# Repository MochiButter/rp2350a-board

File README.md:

# rp2350a-board
A simple development board featuring the rp2350a microcontroller.

## Changes from the Pico 2

- PICO_DEFAULT_LED_PIN is now IO15
- Flash size increased to 128Mbit
- ESD protection on the usb data wires
- A reset button
- An LDO voltage regulator
- USB-C receptacle

`blink` and `hello_usb` of the examples worked on the board as expected.

Licensed under CERN-OHL-P v2 or later

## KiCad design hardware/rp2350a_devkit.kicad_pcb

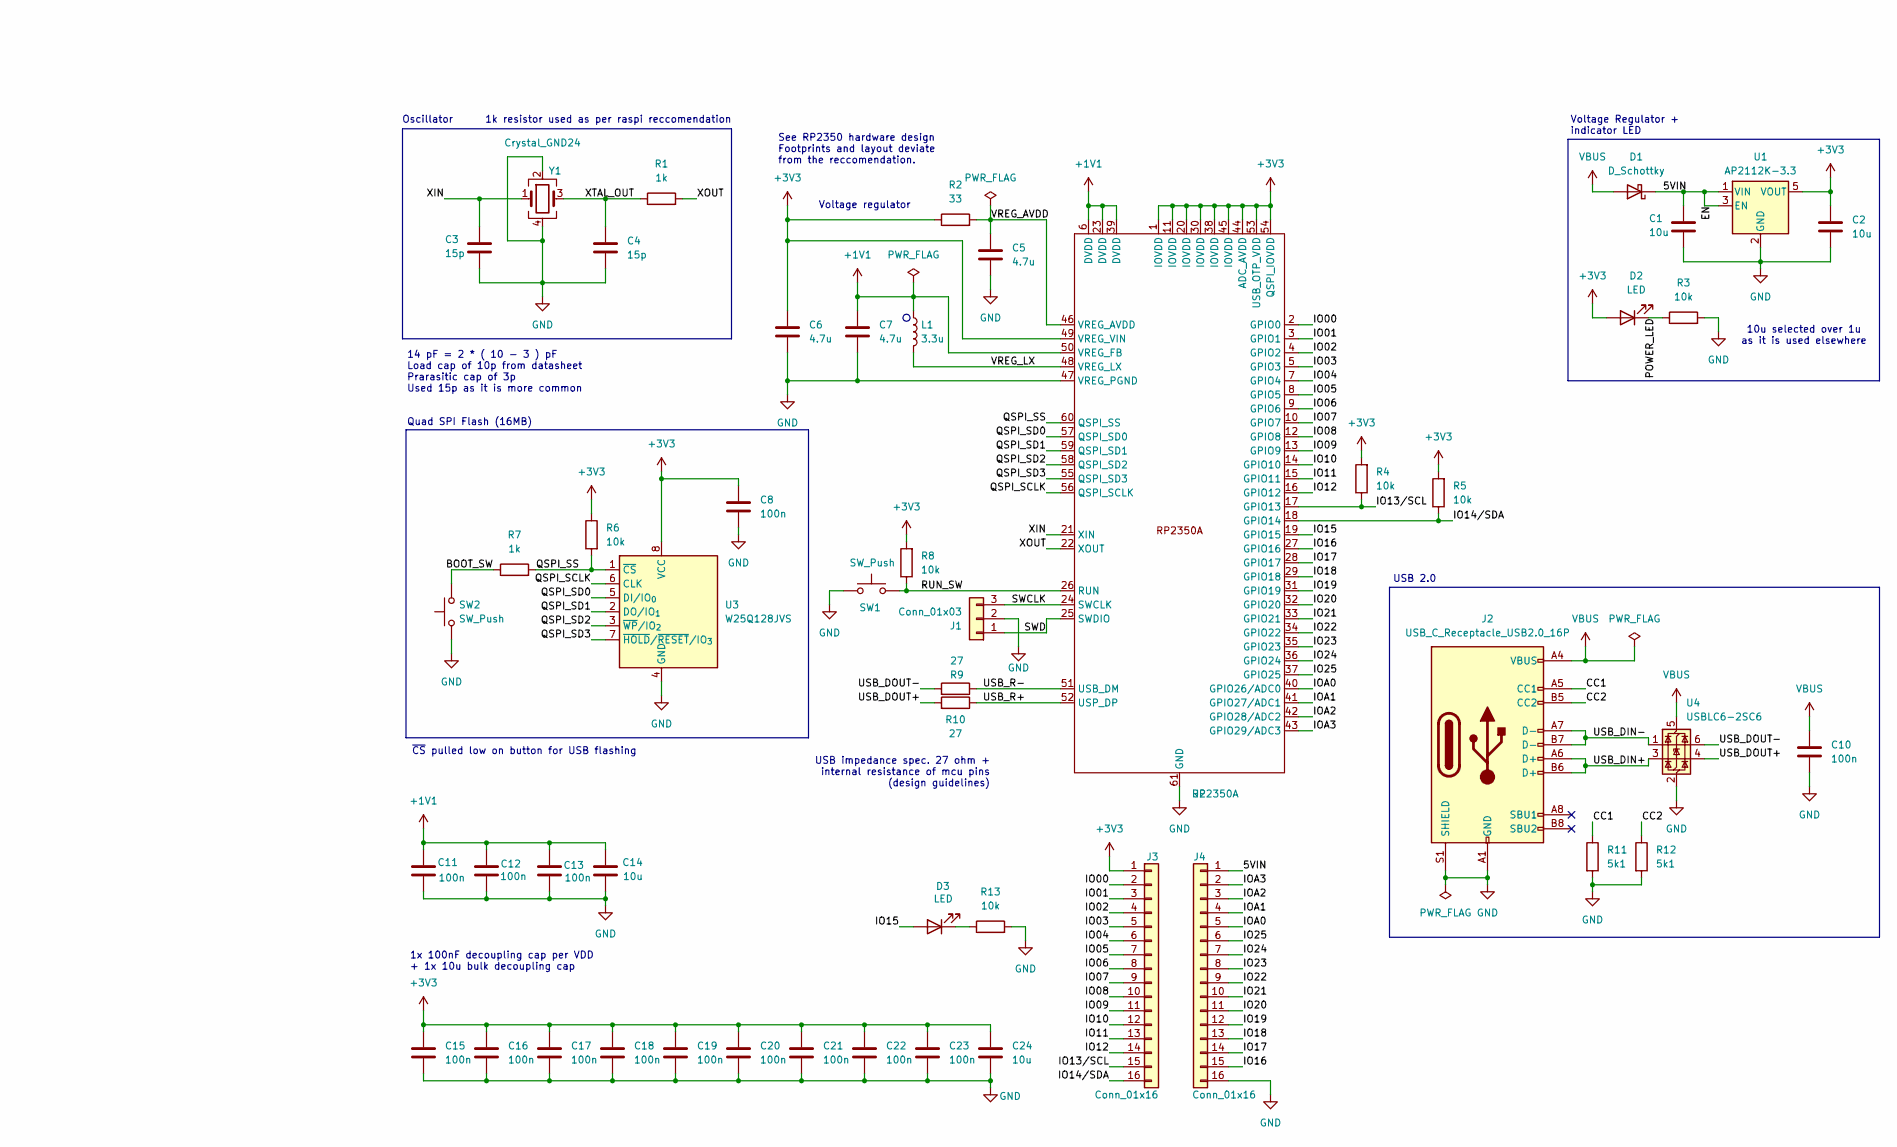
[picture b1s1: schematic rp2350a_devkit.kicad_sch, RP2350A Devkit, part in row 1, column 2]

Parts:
C1, C2, C14, C24: 10u; C_0805_2012Metric
C3, C4: 15p; C_0603_1608Metric
C5, C6, C7: 4.7u; C_0603_1608Metric
C8, C10, C11, C12, C13, C15, C16, C17, C18, C19, C20, C21, C22, C23: 100n; C_0603_1608Metric
D1: D_Schottky; D_SOD-123; LCSC PN C64885
D2, D3: LED; LED_0603_1608Metric
H1, H2, H3, H4: MountingHole; MountingHole_2.2mm_M2
J1: Conn_01x03; PinHeader_1x03_P2.54mm_Vertical
J2: USB_C_Receptacle_USB2.0_16P; USB_C_Receptacle_G-Switch_GT-USB-7010ASV; LCSC PN C2988369
J3, J4: Conn_01x16; PinHeader_1x16_P2.54mm_Vertical
L1: 3.3u; AOTA-B201610S3R3-101-T; LCSC PN C42411119
R1, R7: 1k; R_0603_1608Metric
R2: 33; R_0603_1608Metric
R3, R4, R5, R6, R8, R13: 10k; R_0603_1608Metric
R9, R10: 27; R_0603_1608Metric
R11, R12: 5k1; R_0603_1608Metric
SW1, SW2: SW_Push; TS-1088-AR02016; LCSC PN C720477
U1: AP2112K-3.3; SOT-23-5; LCSC PN C51118
U2: RP2350A; QFN-60-1EP_7x7mm_P0.4mm_EP3.4x3.4mm; LCSC PN C42411118
U3: W25Q128JVS; SOIC-8_5.3x5.3mm_P1.27mm; LCSC PN C113767
U4: USBLC6-2SC6; SOT-23-6; LCSC PN C7519
Y1: Crystal_GND24; Crystal_SMD_3225-4Pin_3.2x2.5mm; LCSC PN C20625731

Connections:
+1V1: C7.1, C11.1, C12.1, C13.1, C14.1, L1.1, U2.6 (DVDD), U2.23 (DVDD), U2.39 (DVDD), U2.50 (VREG_FB)
+3V3: C2.1, C6.1, C8.1, C15.1, C16.1, C17.1, C18.1, C19.1, C20.1, C21.1, C22.1, C23.1, C24.1, D2.2 (A), J3.1, R2.1, R4.2, R5.2, R6.1, R8.2, U1.5 (VOUT), U2.1 (IOVDD), U2.11 (IOVDD), U2.20 (IOVDD), U2.30 (IOVDD), U2.38 (IOVDD), U2.44 (ADC_AVDD), U2.45 (IOVDD), U2.49 (VREG_VIN), U2.53 (USB_OTP_VDD), U2.54 (QSPI_IOVDD), U3.8 (VCC)
/5VIN: C1.1, D1.1 (K), J4.1, U1.1 (VIN), U1.3 (EN)
/BOOT_SW: R7.1, SW2.1; also elsewhere on the board
/CC1: J2.A5 (CC1), R11.1
/CC2: J2.B5 (CC2), R12.1
/IO00: J3.2, U2.2 (GPIO0)
/IO01: J3.3, U2.3 (GPIO1)
/IO02: J3.4, U2.4 (GPIO2)
/IO03: J3.5, U2.5 (GPIO3)
/IO04: J3.6, U2.7 (GPIO4)
/IO05: J3.7, U2.8 (GPIO5)
/IO06: J3.8, U2.9 (GPIO6)
/IO07: J3.9, U2.10 (GPIO7)
/IO08: J3.10, U2.12 (GPIO8)
/IO09: J3.11, U2.13 (GPIO9)
/IO10: J3.12, U2.14 (GPIO10)
/IO11: J3.13, U2.15 (GPIO11)
/IO12: J3.14, U2.16 (GPIO12)
/IO13/SCL: J3.15, R4.1, U2.17 (GPIO13)
/IO14/SDA: J3.16, R5.1, U2.18 (GPIO14)
/IO15: D3.2 (A), U2.19 (GPIO15)
/IO16: J4.15, U2.27 (GPIO16)
/IO17: J4.14, U2.28 (GPIO17)
/IO18: J4.13, U2.29 (GPIO18)
/IO19: J4.12, U2.31 (GPIO19)
/IO20: J4.11, U2.32 (GPIO20)
/IO21: J4.10, U2.33 (GPIO21)
/IO22: J4.9, U2.34 (GPIO22)
/IO23: J4.8, U2.35 (GPIO23)
/IO24: J4.7, U2.36 (GPIO24)
/IO25: J4.6, U2.37 (GPIO25)
/IOA0: J4.5, U2.40 (GPIO26/ADC0)
/IOA1: J4.4, U2.41 (GPIO27/ADC1)
/IOA2: J4.3, U2.42 (GPIO28/ADC2)
/IOA3: J4.2, U2.43 (GPIO29/ADC3)
/POWER_LED: D2.1 (K), R3.1
/QSPI_SCLK: U2.56 (QSPI_SCLK), U3.6 (CLK)
/QSPI_SD0: U2.57 (QSPI_SD0), U3.5 (DI/IO_{0})
/QSPI_SD1: U2.59 (QSPI_SD1), U3.2 (DO/IO_{1})
/QSPI_SD2: U2.58 (QSPI_SD2), U3.3 (~WP/IO_{2})
/QSPI_SD3: U2.55 (QSPI_SD3), U3.7 (~HOLD/~RESET/IO_{3})
/QSPI_SS: R6.2, R7.2, U2.60 (QSPI_SS), U3.1 (~CS)
/RUN_SW: R8.1, SW1.1, U2.26 (RUN); also elsewhere on the board
/SWCLK: J1.3, U2.24 (SWCLK)
/SWD: J1.1, U2.25 (SWDIO)
/USB_DIN+: J2.A6 (D+), J2.B6 (D+), U4.3 (I/O2)
/USB_DIN-: J2.A7 (D-), J2.B7 (D-), U4.1 (I/O1)
/USB_DOUT+: R10.2, U4.4 (I/O2)
/USB_DOUT-: R9.2, U4.6 (I/O1)
/USB_R+: R10.1, U2.52 (USP_DP)
/USB_R-: R9.1, U2.51 (USB_DM)
/VREG_AVDD: C5.1, R2.2, U2.46 (VREG_AVDD)
/VREG_LX: L1.2, U2.48 (VREG_LX)
/XIN: C3.1, U2.21 (XIN), Y1.1
/XOUT: R1.2, U2.22 (XOUT)
/XTAL_OUT: C4.1, R1.1, Y1.3
GND: C1.2, C2.2, C3.2, C4.2, C5.2, C6.2, C7.2, C8.2, C10.2, C11.2, C12.2, C13.2, C14.2, C15.2, C16.2, C17.2, C18.2, C19.2, C20.2, C21.2, C22.2, C23.2, C24.2, J1.2, J2.A1 (GND), J2.A12 (GND), J2.B1 (GND), J2.B12 (GND), J2.S1 (SHIELD), J4.16, R3.2, R11.2, R12.2, R13.2, SW1.2, SW2.2, U1.2 (GND), U2.47 (VREG_PGND), U2.61 (GND), U3.4 (GND), U4.2 (GND), Y1.2, Y1.4; also elsewhere on the board
unnamed: D3.1 (K), R13.1
VBUS: C10.1, D1.2 (A), J2.A4 (VBUS), J2.A9 (VBUS), J2.B4 (VBUS), J2.B9 (VBUS), U4.5 (VBUS)

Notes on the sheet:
10u selected over 1u as it is used elsewhere
Quad SPI Flash (16MB)
1x 100nF decoupling cap per VDD + 1x 10u bulk decoupling cap
Voltage regulator
Voltage Regulator + indicator LED
USB 2.0
~{CS} pulled low on button for USB flashing
See RP2350 hardware design Footprints and layout deviate from the reccomendation.
14 pF = 2 * ( 10 - 3 ) pF Load cap of 10p from datasheet Prarasitic cap of 3p Used 15p as it is more common
USB impedance spec. 27 ohm + internal resistance of mcu pins (design guidelines)
Oscillator
1k resistor used as per raspi reccomendation

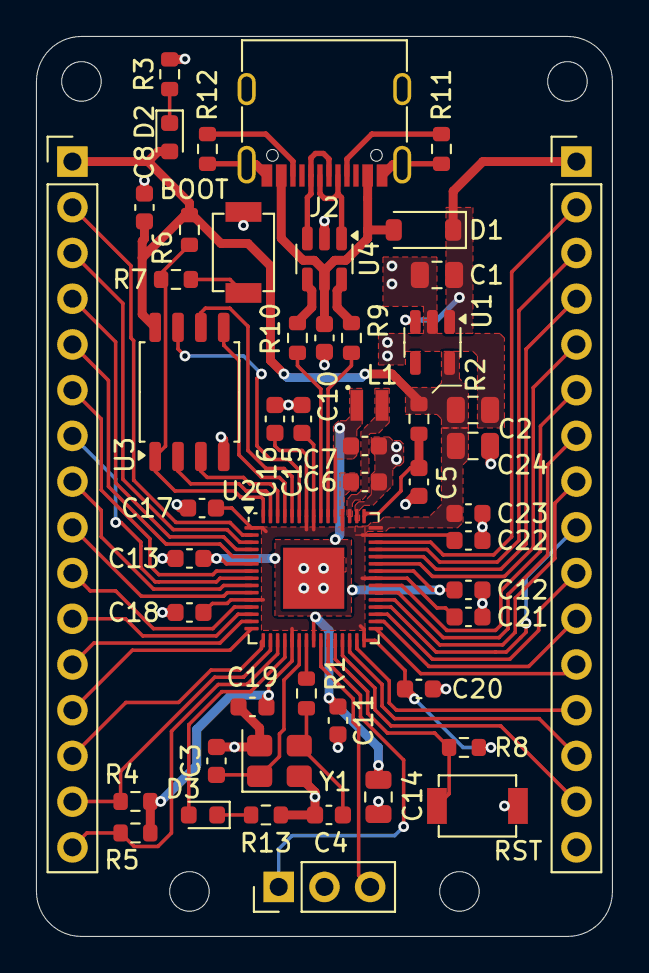
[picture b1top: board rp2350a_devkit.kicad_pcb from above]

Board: 2 copper layers, 32.0 x 50.0 mm, 55 parts (0 on the bottom side), 60 nets.

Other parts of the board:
BOOT: SW_Push; TS-1088-AR02016
RST: SW_Push; TS-1088-AR02016

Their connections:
/BOOT_SW: BOOT.1; also elsewhere on the board
/RUN_SW: RST.1; also elsewhere on the board
GND: BOOT.2, RST.2; also elsewhere on the board

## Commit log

2025-06-15 add license
2025-06-17 add hw design files
2025-06-18 add images and files for v1.0a
2025-06-22 re-routed pcb for a better ground plane
2025-06-24 update 3d pcb image, fix silkscreen placement and resistor values
2025-06-25 changed button footprint
2025-07-17 added manufactured board picture
